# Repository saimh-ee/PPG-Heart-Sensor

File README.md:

# PPG Heart Sensor PCB

A custom KiCad PCB developed as an extension of a UBC ENGR 352 Microelectronics II photoplethysmography (PPG) heart-rate sensing project. The original course work focused on simulation and breadboard prototyping, and this PCB was designed to turn that work into a cleaner hardware implementation.

## Overview

This project is based on a PPG sensing approach that uses an infrared emitter and photodiode to detect pulse-related changes optically. The original course work focused on simulation and breadboard prototyping, while this repository focuses on the PCB design, supporting simulation files, fabrication outputs, and project visuals.

## Main Component

- MCP601 op-amp

## Repository Contents

- **Hardware/**: KiCad schematic, PCB, project file, and footprint library
- **Simulation/**: LTspice simulation file
- **Fabrication/**: manufacturing package used for PCB ordering
- **Docs/**: schematic image, PCB layout, 3D render, and breadboard prototype photos

## Current Status

- LTspice simulation completed
- Breadboard prototype completed
- PCB designed in KiCad
- Fabrication files generated and submitted
- Final PCB assembly and hardware validation pending board arrival

## Project Images

### 3D Render

### PCB Layout

### Schematic

### Breadboard Prototype

## Notes

This repository documents both the original prototype stage and the PCB design work completed afterward. The PCB was created as an extra step beyond the base lab requirement in order to package the design into a more polished hardware form.

## Tools Used

- KiCad
- LTspice
- Git / GitHub

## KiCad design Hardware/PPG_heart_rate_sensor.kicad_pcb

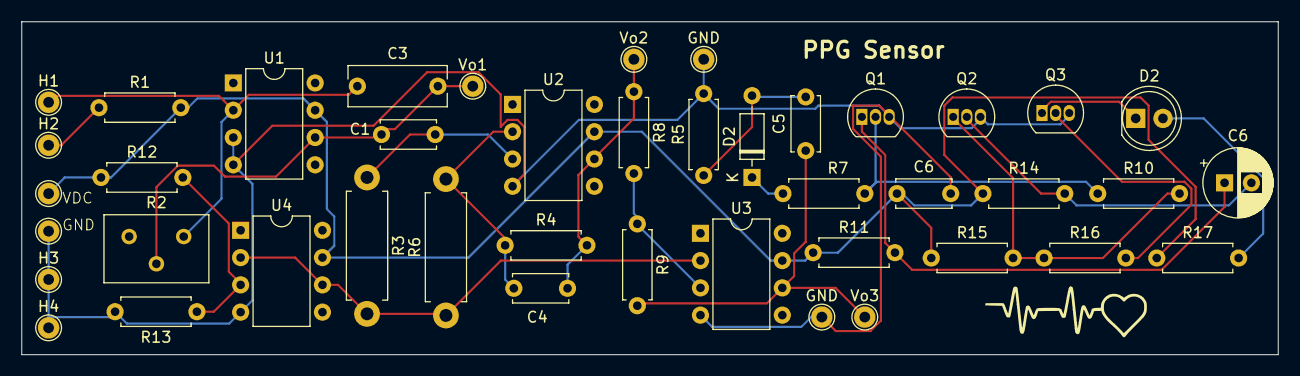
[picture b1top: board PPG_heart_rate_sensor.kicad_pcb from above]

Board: 2 copper layers, 117.0 x 31.0 mm, 43 parts (0 on the bottom side), 21 nets.

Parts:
C1, C5, C6#2: C; C_Disc_D5.0mm_W2.5mm_P5.00mm
C3: C; C_Rect_L9.0mm_W3.6mm_P7.50mm_MKT
C4: C4; C_Disc_D5.0mm_W2.5mm_P5.00mm
C6: C; CP_Radial_D6.3mm_P2.50mm
D2: D; D_DO-35_SOD27_P7.62mm_Horizontal
D2#2: LED; LED_D5.0mm
GND: MountingHole_Pad; TestPoint_THTPad_D2.0mm_Drill1.0mm
GND#2: MountingHole_Pad; TestPoint_THTPad_D2.0mm_Drill1.0mm
H1, H3, H3#2, H4, H5, H6: MountingHole_Pad; TestPoint_THTPad_D2.0mm_Drill1.0mm
Q1, Q2, Q3: NPN; TO-92_Inline
R1, R4, R5, R7, R8, R9, R10, R11, R12, R13, R14, R15, R16, R17: R; R_Axial_DIN0207_L6.3mm_D2.5mm_P7.62mm_Horizontal
R2: R; Potentiometer_Bourns_3299Y_Vertical
R3, R6: R; R_Axial_DIN0411_L9.9mm_D3.6mm_P12.70mm_Horizontal
U1, U2, U3, U4: MCP601; DIP-8_W7.62mm
Vo1, Vo2, Vo3: MountingHole_Pad; TestPoint_THTPad_D2.0mm_Drill1.0mm

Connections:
GND: C6#2.2, GND.1, GND#2.1, H3#2.1, H4.1, H6.1, Q1.3 (E), Q2.3 (E), Q3.3 (E), R5.2, R13.2, U1.3, U1.4, U2.4, U3.4, U4.4
unnamed: C3.1, H1.1, R2.1, U1.2
unnamed: C1.1, C3.2, R2.2, U1.6, Vo1.1
unnamed: C1.2, R3.1, U2.3
unnamed: C4.1, R4.1, R6.2, U2.2
unnamed: C4.2, R4.2, R8.1, U2.6, Vo2.1
unnamed: C5.1, R9.2, U3.6, Vo3.1
unnamed: C5.2, D2.2 (A), R5.1
unnamed: D2.1 (K), R7.1
unnamed: D2#2.2 (A), R17.2
unnamed: D2#2.1 (K), Q3.1 (C)
unnamed: H3.1, R1.1
unnamed: R12.2, R13.1, U4.3
unnamed: R8.2, R9.1, U3.3
unnamed: Q1.2 (B), R7.2, R10.1
unnamed: C6.1, Q1.1 (C), R11.2
unnamed: C6.2, Q2.2 (B), R14.2
unnamed: Q2.1 (C), R10.2, R15.2, R16.1
unnamed: Q3.2 (B), R16.2
VDC: C6#2.1, H5.1, R1.2, R11.1, R12.1, R14.1, R15.1, R17.1, U1.7, U2.7, U3.7, U4.7
Vref: R3.2, R6.1, U3.2, U4.2, U4.6
